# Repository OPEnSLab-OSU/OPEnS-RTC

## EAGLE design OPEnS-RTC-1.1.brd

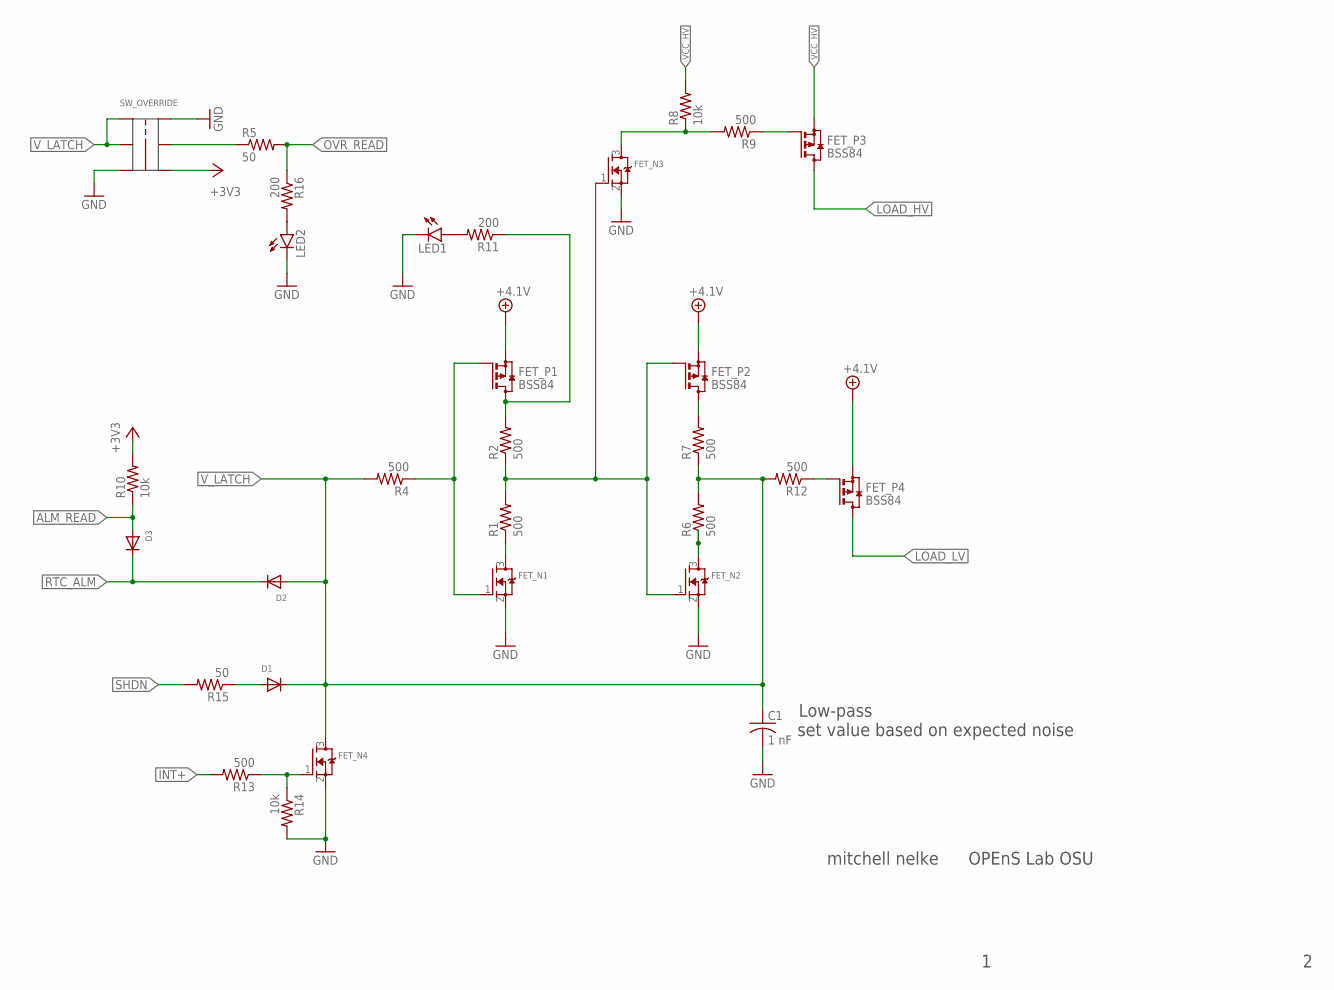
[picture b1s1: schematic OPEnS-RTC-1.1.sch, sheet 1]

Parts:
C1: 1 nF; C0805
D1, D2, D3: DIODESOD-123; SOD-123
FET_N1, FET_N2, FET_N3, FET_N4: MOSFET-NREFLOW; SOT23
FET_P1, FET_P2, FET_P3, FET_P4: BSS84; SOT23
LED1, LED2: LEDSMT1206; 1206
R1, R2, R4, R6, R7, R9, R12, R13: 500; R0805
R5, R15: 50; R0805
R8, R10, R14: 10k; R0805
R11, R16: 200; R0805
SW_OVERRIDE: JS202011JCQN; VERTICAL_MNT_SMT-J

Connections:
+3V3: R10.2, SW_OVERRIDE.A_; also elsewhere on the board
+4.1V: FET_P1.2 (S), FET_P2.2 (S), FET_P4.2 (S); also elsewhere on the board
ALM_READ: D3.A, R10.1; also elsewhere on the board
GND: C1.2, FET_N1.2 (S), FET_N2.2 (S), FET_N3.2 (S), FET_N4.2 (S), LED1.C, LED2.C, R14.2, SW_OVERRIDE.A, SW_OVERRIDE.B_; also elsewhere on the board
INT+: R13.2; also elsewhere on the board
LOAD_HV: FET_P3.3 (D); also elsewhere on the board
LOAD_LV: FET_P4.3 (D); also elsewhere on the board
unnamed: FET_P1.3 (D), R2.2, R11.1
unnamed: FET_N1.3 (D), R1.1
unnamed: FET_N1.1 (G), FET_P1.1 (G), R4.1
unnamed: FET_N2.1 (G), FET_N3.1 (G), FET_P2.1 (G), R1.2, R2.1
unnamed: FET_N3.3 (D), R8.1, R9.2
unnamed: FET_P2.3 (D), R7.2
unnamed: FET_N2.3 (D), R6.1
unnamed: FET_P3.1 (G), R9.1
unnamed: LED1.A, R11.2
unnamed: FET_P4.1 (G), R12.1
unnamed: D1.A, R15.1
unnamed: FET_N4.1 (G), R13.1, R14.1
unnamed: LED2.A, R16.2
unnamed: R5.1, SW_OVERRIDE.COM_
OVR_READ: R5.2, R16.1; also elsewhere on the board
RTC_ALM: D2.C, D3.C; also elsewhere on the board
SHDN: R15.2; also elsewhere on the board
VCC_HV: FET_P3.2 (S), R8.2; also elsewhere on the board
V_LATCH: C1.1, D1.C, D2.A, FET_N4.3 (D), R4.2, R6.2, R7.1, R12.2, SW_OVERRIDE.B, SW_OVERRIDE.COM; also elsewhere on the board

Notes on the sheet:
mitchell nelke
OPEnS Lab OSU
Low-pass
set value based on expected noise

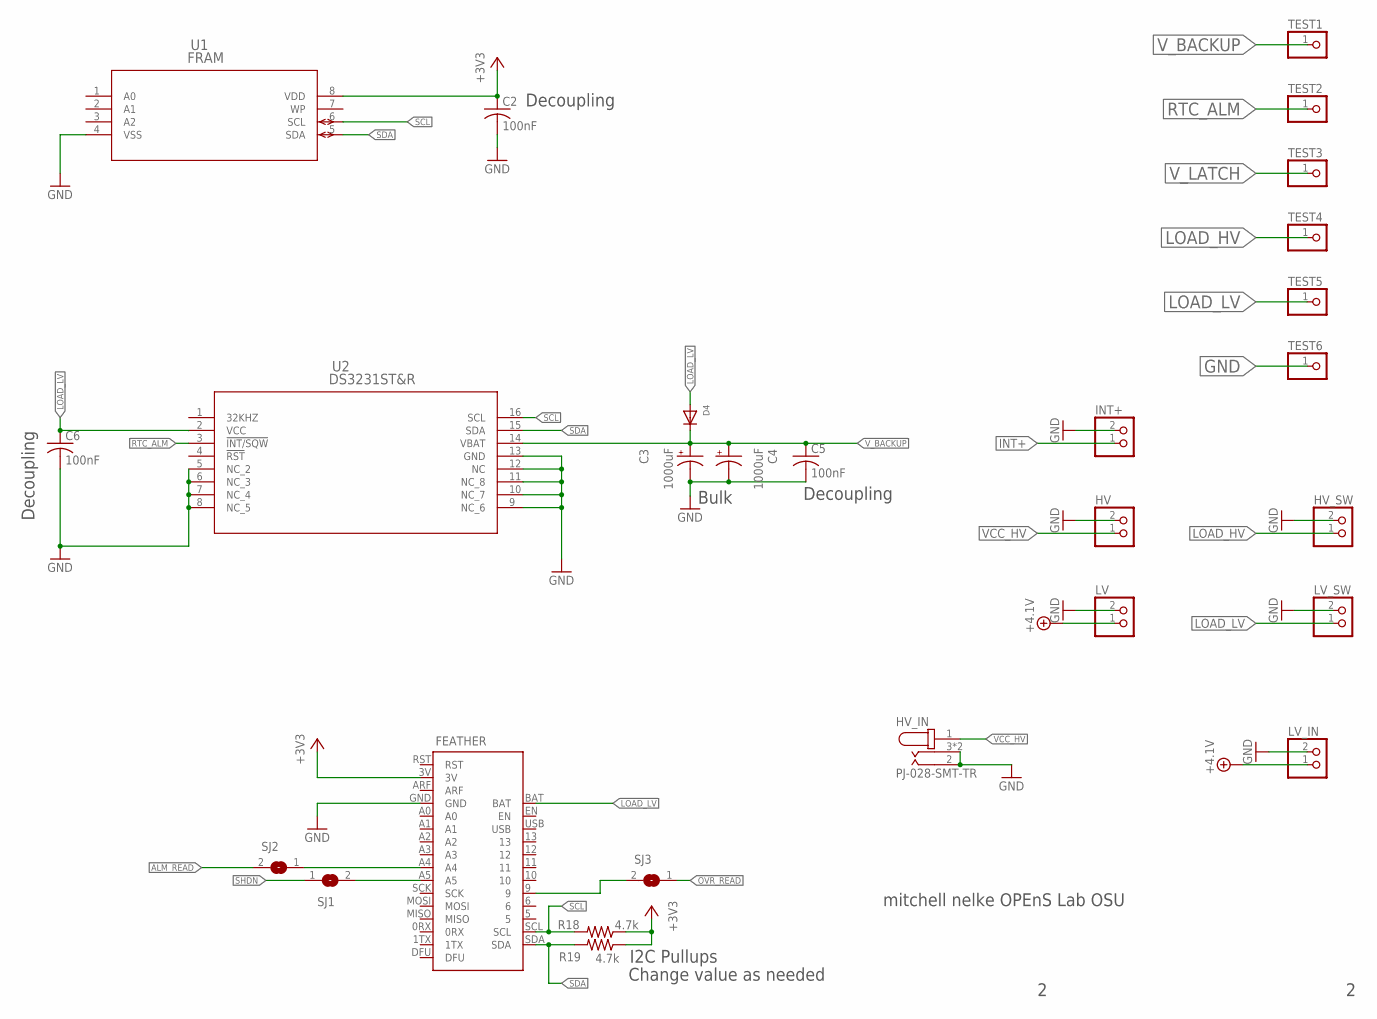
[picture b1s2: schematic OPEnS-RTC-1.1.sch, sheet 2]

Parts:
C2, C5, C6: 100nF; C0805
C3, C4: 1000uF; E3,5-8
D4: DIODESOD-123; SOD-123
FEATHER: BLUEFRUIT_M0; BLUEFRUIT_MO
HV: JST_2PIN-SMT; JST-PH-2-SMT
HV_IN: PJ-028-SMT-TR; CUI_PJ-028-SMT-TR
HV_SW: JST_2PIN-SMT; JST-PH-2-SMT
INT+: JST_2PIN-SMT; JST-PH-2-SMT
LV: JST_2PIN-SMT; JST-PH-2-SMT
LV_IN: JST_2PIN-SMT; JST-PH-2-SMT
LV_SW: JST_2PIN-SMT; JST-PH-2-SMT
R18, R19: 4.7k; M0805
SJ1, SJ2, SJ3: SJ
TEST1, TEST2, TEST3, TEST4, TEST5, TEST6: PINHD-1X1; 1X01
U1: FRAM; FPT-8P-M02
U2: DS3231ST&R; 21-0042B_16

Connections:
+3V3: C2.1, FEATHER.3V, R18.1, R19.1, U1.8 (VDD); also elsewhere on the board
+4.1V: LV.1 (2), LV_IN.1 (2); also elsewhere on the board
ALM_READ: SJ2.2; also elsewhere on the board
GND: C2.2, C3.-, C4.-, C5.2, C6.2, FEATHER.GND, HV.2 (1), HV_IN.2, HV_IN.3, HV_IN.3.1 (3), HV_SW.2 (1), INT+.2 (1), LV.2 (1), LV_IN.2 (1), LV_SW.2 (1), TEST6.1, U1.4 (VSS), U2.5 (NC_2), U2.6 (NC_3), U2.7 (NC_4), U2.8 (NC_5), U2.9 (NC_6), U2.10 (NC_7), U2.11 (NC_8), U2.12 (NC), U2.13 (GND); also elsewhere on the board
INT+: INT+.1 (2); also elsewhere on the board
LOAD_HV: HV_SW.1 (2), TEST4.1; also elsewhere on the board
LOAD_LV: C6.1, D4.A, FEATHER.BAT, LV_SW.1 (2), TEST5.1, U2.2 (VCC); also elsewhere on the board
unnamed: FEATHER.A4, SJ2.1
unnamed: FEATHER.A5, SJ1.2
unnamed: FEATHER.9, SJ3.2
OVR_READ: SJ3.1; also elsewhere on the board
RTC_ALM: TEST2.1, U2.3 (!INT/SQW); also elsewhere on the board
SCL: FEATHER.SCL, R18.2, U1.6 (SCL), U2.16 (SCL)
SDA: FEATHER.SDA, R19.2, U1.5 (SDA), U2.15 (SDA)
SHDN: SJ1.1; also elsewhere on the board
VCC_HV: HV.1 (2), HV_IN.1; also elsewhere on the board
V_BACKUP: C3.+, C4.+, C5.1, D4.C, TEST1.1, U2.14 (VBAT)
V_LATCH: TEST3.1; also elsewhere on the board

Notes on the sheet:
mitchell nelke OPEnS Lab OSU
Decoupling
Bulk
I2C Pullups
Change value as needed

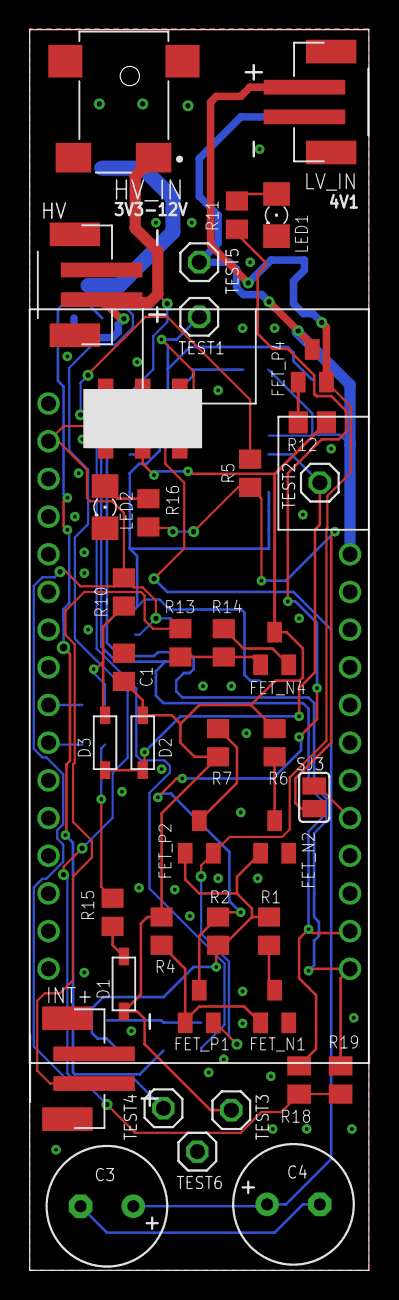
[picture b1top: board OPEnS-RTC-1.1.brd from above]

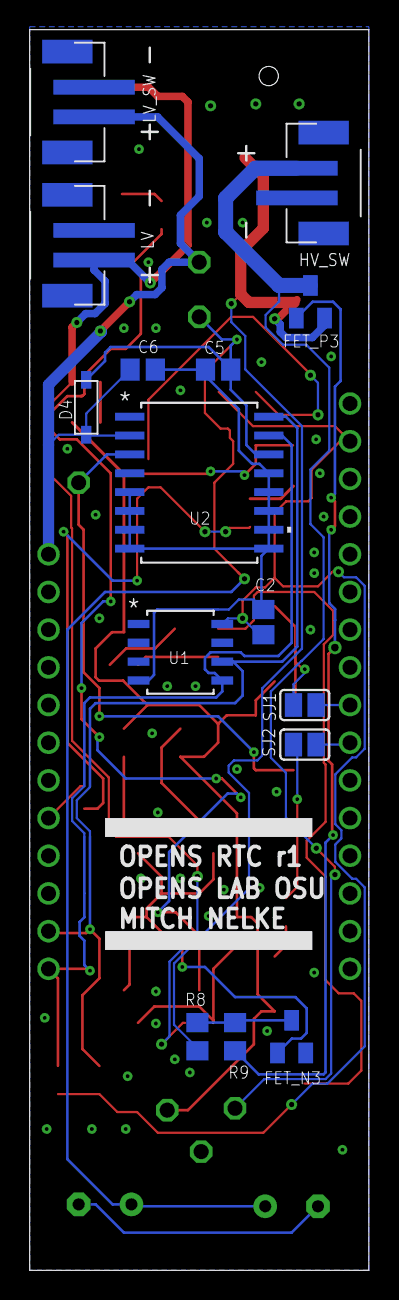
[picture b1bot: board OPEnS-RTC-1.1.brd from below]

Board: 2 copper layers, 22.9 x 83.6 mm, 57 parts (15 on the bottom side), 32 nets.

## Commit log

2019-06-24 First upload switching from OPEnS Power to OPEnS RTC
2019-06-24 Create bluefruit_m0.lbr
    quickfix - added Bluefruit_m0.lbr. Will converge to single eagle library at a later date.
2019-06-27 Revised components and labels.
    Added documentation (with BoM) as a .docx and .pdf. Swapped pins on JST connectors. Removed pointless pullup resistor, added current limiting resistor for LED. Swapped 2mm barrel jack for 0.9mm x 3.2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
